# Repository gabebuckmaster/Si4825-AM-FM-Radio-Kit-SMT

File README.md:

# Si4825-AM-FM-Radio-Kit-SMT
Si4825 AM/FM Radio Kit (SMT)

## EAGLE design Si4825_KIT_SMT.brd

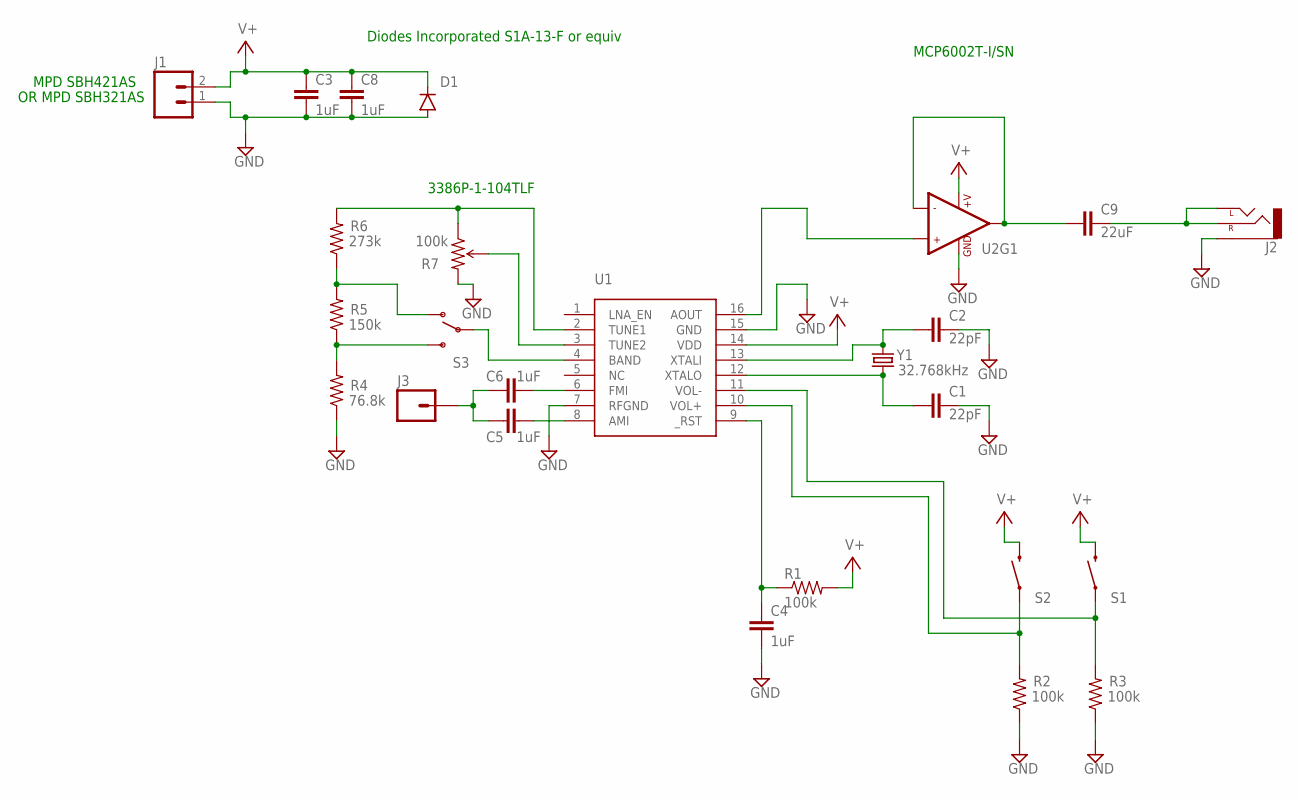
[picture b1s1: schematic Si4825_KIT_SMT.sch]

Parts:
C1, C2: 22pF; 0805
C3, C4, C5, C6, C8: 1uF; 0805
C9: 22uF; 0805
D1: DIODESMA; SMA-DIODE
J1: M02PTH; 1X02
J2: AUDIO-JACKPTH; AUDIO-JACK
J3: M01PTH; 1X01
R1, R2, R3: 100k; 0805
R4: 76.8k; 0805
R5: 150k; 0805
R6: 273k; 0805
R7: 100k; BOURNS_3386P
S1, S2: SWITCH-MOMENTARY-2PTH; TACTILE-PTH
S3: SWITCH-SPDTPTH; SWITCH-SPDT
U1: SI4825; SO16
U2: LMV358SOIC; SO08
Y1: 32.768kHz; TC26H

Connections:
GND: C1.2, C2.2, C3.2, C4.2, C8.2, D1.A, J1.1, J2.SLEEVE, R2.1, R3.1, R4.1, R7.P$3 (CW), U1.7 (RFGND), U1.15 (GND), U2.4 (GND)
unnamed: C5.2, U1.8 (AMI)
unnamed: C1.1, U1.12 (XTALO), Y1.2
unnamed: C2.1, U1.13 (XTALI), Y1.1
unnamed: C4.1, R1.1, U1.9 (_RST)
unnamed: R2.2, S2.1, U1.10 (VOL+)
unnamed: R3.2, S1.1, U1.11 (VOL-)
unnamed: S3.2, U1.4 (BAND)
unnamed: R4.2, R5.1, S3.3 (S)
unnamed: R5.2, R6.1, S3.1 (O)
unnamed: R6.2, R7.P$1 (CCW), U1.2 (TUNE1)
unnamed: C6.2, U1.6 (FMI)
unnamed: R7.P$2 (WIPER), U1.3 (TUNE2)
unnamed: C9.2, J2.RING (RIGHT), J2.TIP (LEFT)
unnamed: U1.16 (AOUT), U2.3 (+IN1)
unnamed: C5.1, C6.1, J3.1
unnamed: C9.1, U2.1 (OUT1), U2.2 (-IN1)
V+: C3.1, C8.1, D1.C, J1.2, R1.2, S1.3 (2), S2.3 (2), U1.14 (VDD), U2.8 (+V)

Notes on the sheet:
3386P-1-104TLF
MPD SBH421AS
OR MPD SBH321AS
Diodes Incorporated S1A-13-F or equiv
MCP6002T-I/SN

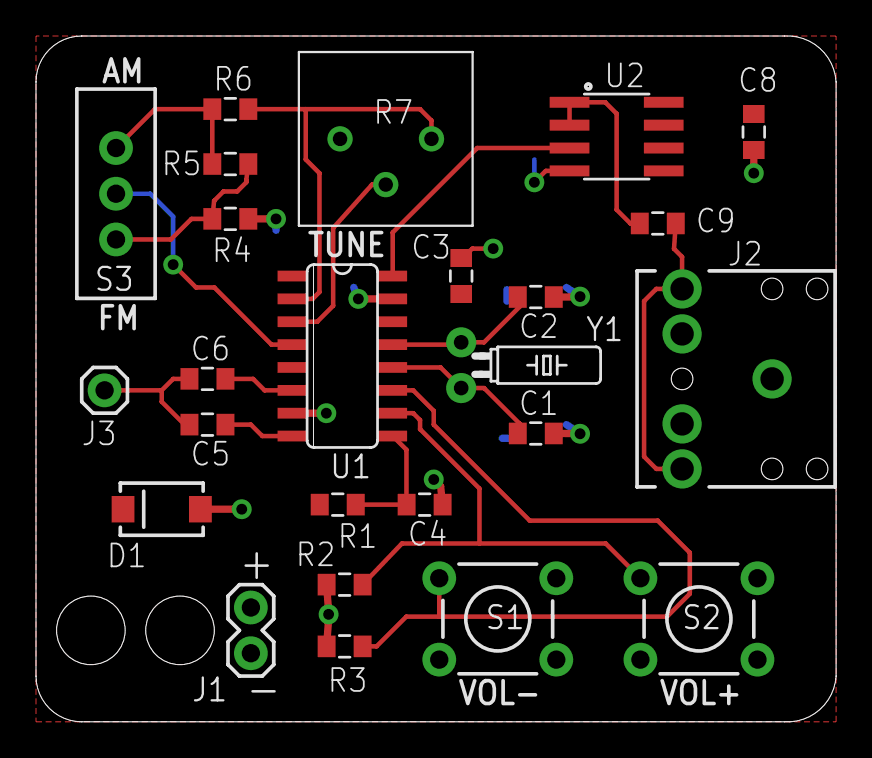
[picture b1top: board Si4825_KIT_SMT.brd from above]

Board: 2 copper layers, 44.5 x 38.1 mm, 25 parts (0 on the bottom side), 18 nets.

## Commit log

2016-09-21 Update .gitignore
    Get rid of .DS_Store
2016-09-21 Added initial design
2016-10-27 Fixed issues discovered in first build
    - fixed potentiometer footprint
    - bigger strain relief holes: .1” to .15”
    - changed value of C9 (AC coupling capacitor) to 22uF in BOM and
    schematic
    - Removed R8 (jumper to bypass op amp)
    - Increased length of surface mount pads for 0805 components to

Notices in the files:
parts and their libraries:
SparkFun-Passives: Licensing: Creative Commons ShareAlike 4.0 International - https://creativecommons.org/licenses/by-sa/4.0
